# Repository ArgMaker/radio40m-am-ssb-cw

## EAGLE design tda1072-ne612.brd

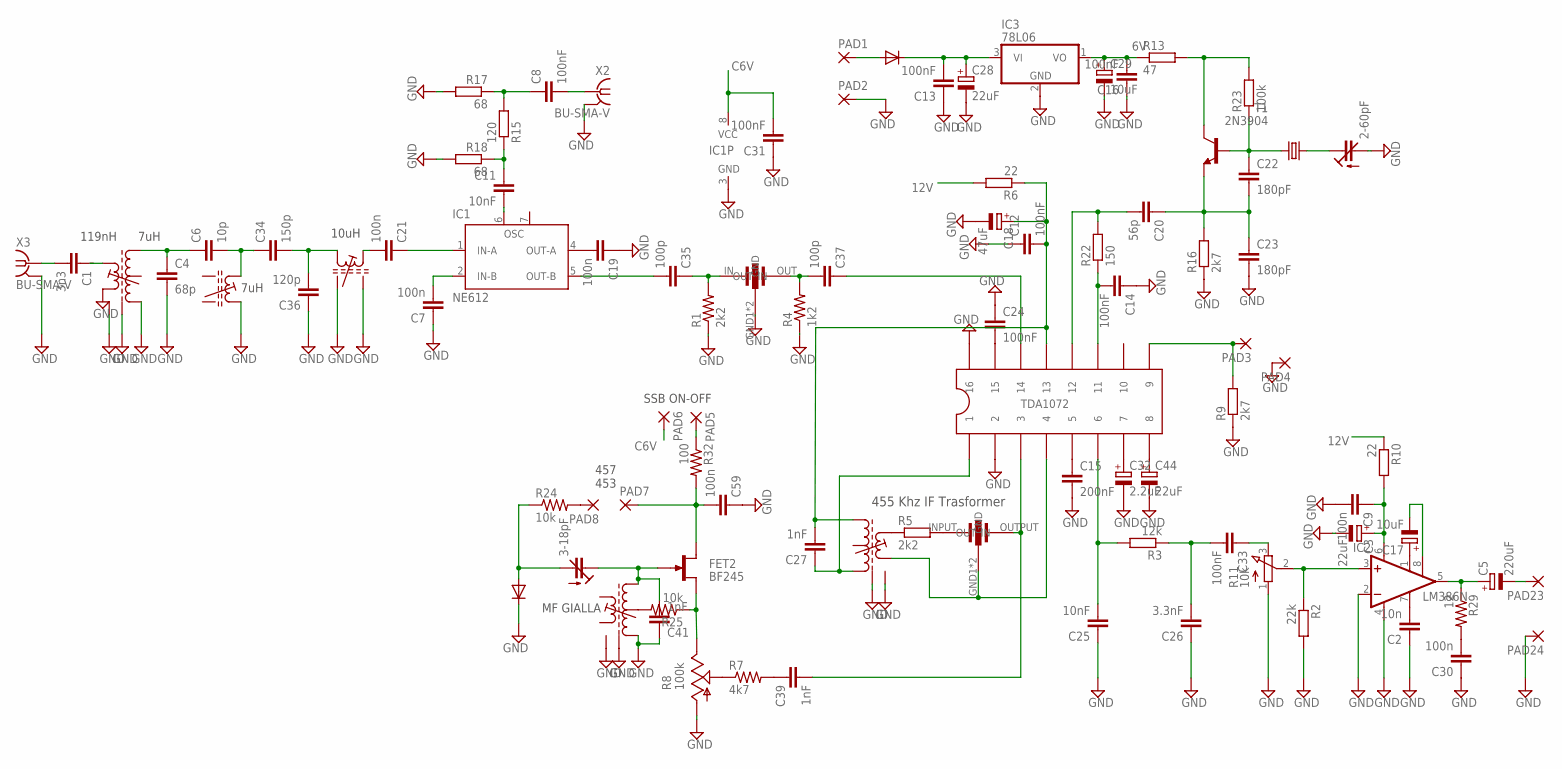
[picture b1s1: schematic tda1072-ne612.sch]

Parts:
10.245MHZ: 10.245 Mhz; HC49/S
C1: 3n3; COND
C2: 10n; COND
C3, C28, C44: 22uF; E1,8-4
C4: 68p; COND
C5: 220uF; E3,5-8
C6: 10p; COND
C7, C9, C19, C21, C59: 100n; COND
C8, C12, C13, C14, C16, C24, C31, C33: 100nF; COND
C11, C25: 10nF; COND
C15: 200nF; CER1
C17, C29: 10uF; E1,8-4
C18: 47uF; E1,8-4
C20: 56p; COND
C22, C23: 180pF; COND
C26: 3.3nF; COND
C27, C39, C41: 1nF; COND
C30: 100n; COND_M
C32: 2.2uF; E1,8-4
C34: 150p; COND
C35, C37: 100p; COND
C36: 120p; COND
C38: 3-18pF; CTRIMTZ03
C55: 2-60pF; CTRIMTZ03
D1: 1N4004; DO41-10
D2: 4148; DO35-7
FET2: BF245
IC1: NE612; DIL08
IC2: LM386N; DIL08
IC3: 78L06; TO92
MF1, MF2, MF3, MF4, MF5: MF-1
PAD1, PAD2: 2,54/1,0
PAD3, PAD4, PAD5, PAD6, PAD7, PAD8, PAD23, PAD24: 1,6/0,9
R1, R5: 2k2; 0204/7
R2: 22k; 0204/7
R3: 12k; 0204/7
R4: 1k2; 0204/7
R6, R10: 22; 0204/7
R7: 4k7; 0204/7
R8: 100k; LI10
R9, R16: 2k7; 0204/7
R11: 10k; 3RP/1610N
R13: 47; 0204/7
R15: 120; 0204/7
R17, R18: 68; 0204/7
R22: 150; 0204/7
R23: 100k; 0204/7
R24, R25: 10k; 0204/7
R29: 12; 0204/7
R32: 100; 0204/7
T1: 2N3904; TO92
TDA1072: TDA1072
U$1: CFM455
U$2: TOY
X2, X3: BU-SMA-V

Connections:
6V: C16.2, C29.+, IC3.1 (VO), R13.1
12V: C13.2, C28.+, D1.C, IC3.3 (VI), R6.2, R10.1
12V1: C3.+, C9.1, IC2.6 (VS), R10.2
C6V: C31.2, IC1.8 (VCC), PAD6.1, R13.2, R23.2, T1.1 (C)
DD: C12.2, C18.+, C27.2, MF4.P$1 (A1), R6.1, TDA1072.13
GND: C2.1, C3.-, C4.2, C7.1, C9.2, C12.1, C13.1, C14.1, C15.2, C16.1, C18.-, C19.1, C23.2, C24.1, C25.1, C26.1, C28.-, C29.-, C30.1, C31.1, C32.-, C36.1, C41.1, C44.-, C55.2 (A), C59.1, D2.C, IC1.3 (GND), IC2.2 (-IN), IC2.4 (GND), IC3.2 (GND), MF1.GND1, MF1.GND2, MF1.S1 (GND2), MF1.S2 (GND2), MF1.S3 (GND2), MF2.P$3 (E1), MF2.P$5 (E2), MF2.P$6, MF2.P$7, MF3.A2, MF4.P$6, MF4.P$7, MF5.P$3 (E1), MF5.P$6, MF5.P$7, PAD2.1, PAD4.1, PAD24.1, R1.1, R2.2, R4.1, R8.A, R9.1, R11.1 (A), R16.1, R17.2, R18.2, TDA1072.2, TDA1072.16, U$2.GND1 (GND), U$2.GND2 (GND), X2.2, X2.3 (2), X2.4 (2), X2.5 (2), X3.2, X3.3 (2), X3.4 (2), X3.5 (2)
unnamed: C21.1, IC1.1 (IN-A)
unnamed: C1.1, MF2.P$4 (A2)
unnamed: C4.1, C6.1, MF2.P$1 (A1)
unnamed: C1.2, X3.1
unnamed: C6.2, C34.1, MF3.A1
unnamed: C37.1, TDA1072.14
unnamed: C34.2, C36.2, MF1.A2
unnamed: C21.2, MF1.A1
unnamed: C7.2, IC1.2 (IN-B)
unnamed: C11.2, IC1.6 (OSC)
unnamed: C33.1, R11.3 (E)
unnamed: C39.2, TDA1072.3, U$1.OUTPUT (OUT)
unnamed: R5.2, U$1.INPUT (IN)
unnamed: C35.2, IC1.5 (OUT-B)
unnamed: D1.A, PAD1.1
unnamed: C8.2, X2.1
unnamed: C19.2, IC1.4 (OUT-A)
unnamed: MF4.P$5 (E2), TDA1072.4, U$1.GND1 (GND), U$1.GND2 (GND)
unnamed: C15.1, TDA1072.5
unnamed: C32.+, TDA1072.7
unnamed: C44.+, TDA1072.8
unnamed: C20.2, R22.2, TDA1072.12
unnamed: C8.1, R15.2, R17.1
unnamed: C20.1, C22.2, C23.1, R16.2, T1.3 (E)
unnamed: C14.2, R22.1, TDA1072.11
unnamed: 10.245MHZ.1, C22.1, R23.1, T1.2 (B)
unnamed: C35.1, R1.2, U$2.IN
unnamed: PAD8.1, R24.2
unnamed: C37.2, R4.2, U$2.OUT
unnamed: C24.2, TDA1072.15
unnamed: C25.2, R3.2, TDA1072.6
unnamed: C26.2, C33.2, R3.1
unnamed: 10.245MHZ.2, C55.1 (E)
unnamed: C17.+, IC2.1 (GAIN)
unnamed: C11.1, R15.1, R18.1
unnamed: MF5.P$2 (Z), R25.2
unnamed: R7.1, R8.S
unnamed: C30.2, R29.2
unnamed: C5.-, PAD23.1
unnamed: C5.+, IC2.5 (OUT), R29.1
unnamed: IC2.3 (+IN), R2.1, R11.2 (S)
unnamed: C2.2, IC2.7 (BYPASS)
unnamed: C17.-, IC2.8 (GAIN)
unnamed: C38.1 (E), C41.2, FET2.G, MF5.P$1 (A1)
unnamed: FET2.S, R8.E, R25.1
unnamed: C38.2 (A), D2.A, R24.1
unnamed: C39.1, R7.2
unnamed: MF4.P$4 (A2), R5.1
unnamed: C59.2, FET2.D, PAD7.1, R32.2
unnamed: C27.1, MF4.P$3 (E1), TDA1072.1
S-METER: PAD3.1, R9.2, TDA1072.9
SSB: PAD5.1, R32.1

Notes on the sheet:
455 Khz IF Trasformer
119nH
7uH
10uH
SSB ON-OFF
MF GIALLA
457 453

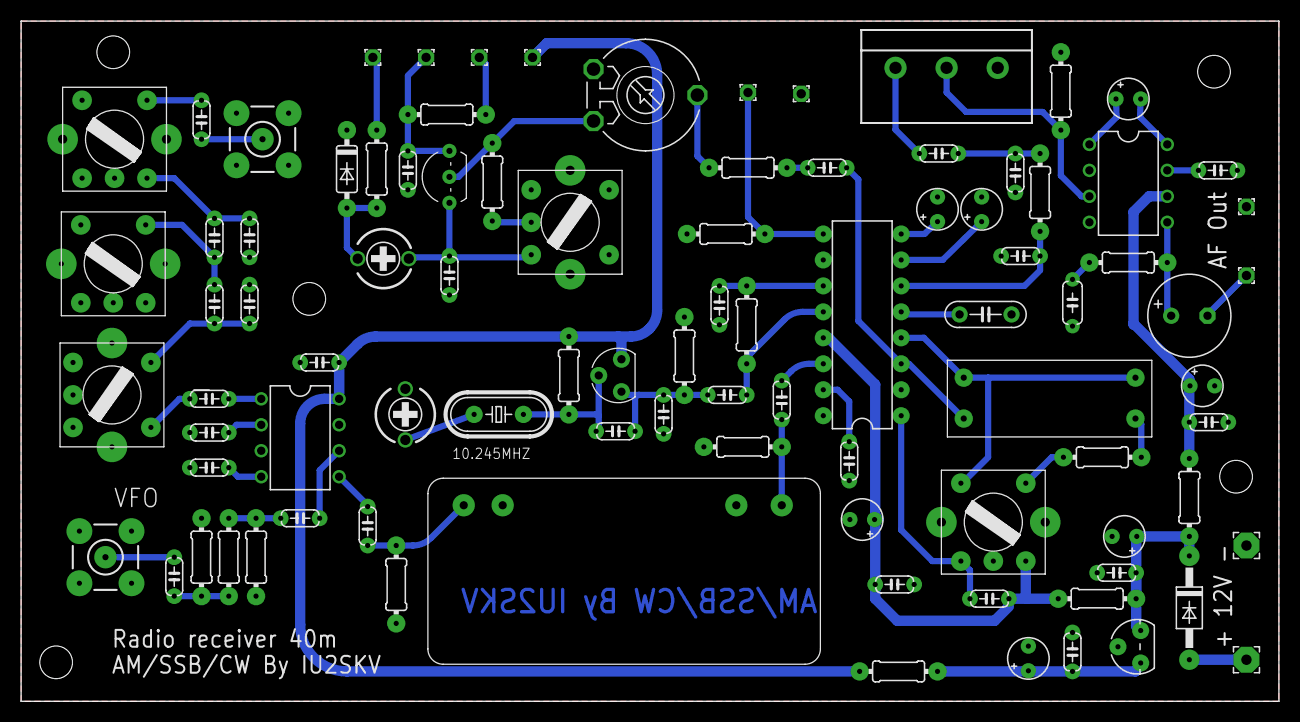
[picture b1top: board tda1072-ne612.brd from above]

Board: 2 copper layers, 123.1 x 66.5 mm, 92 parts (0 on the bottom side), 58 nets.

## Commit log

2024-05-12 Add files via upload
    Prima versione della radio banda 40m AM SSB CW non ancora testato al 100%
